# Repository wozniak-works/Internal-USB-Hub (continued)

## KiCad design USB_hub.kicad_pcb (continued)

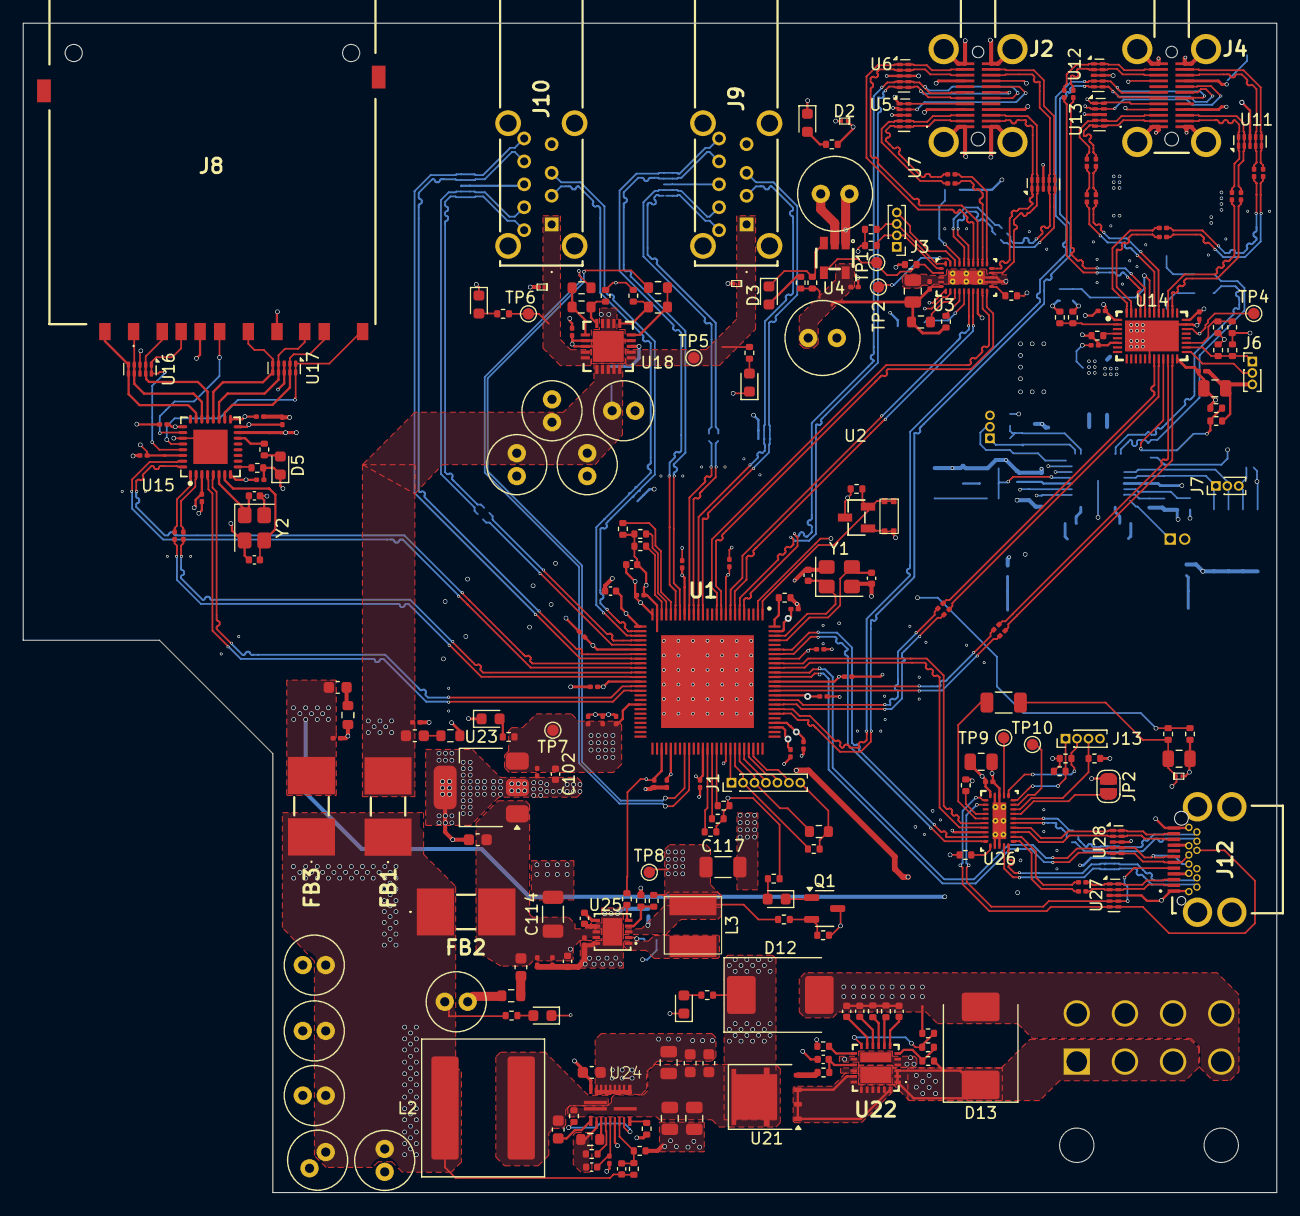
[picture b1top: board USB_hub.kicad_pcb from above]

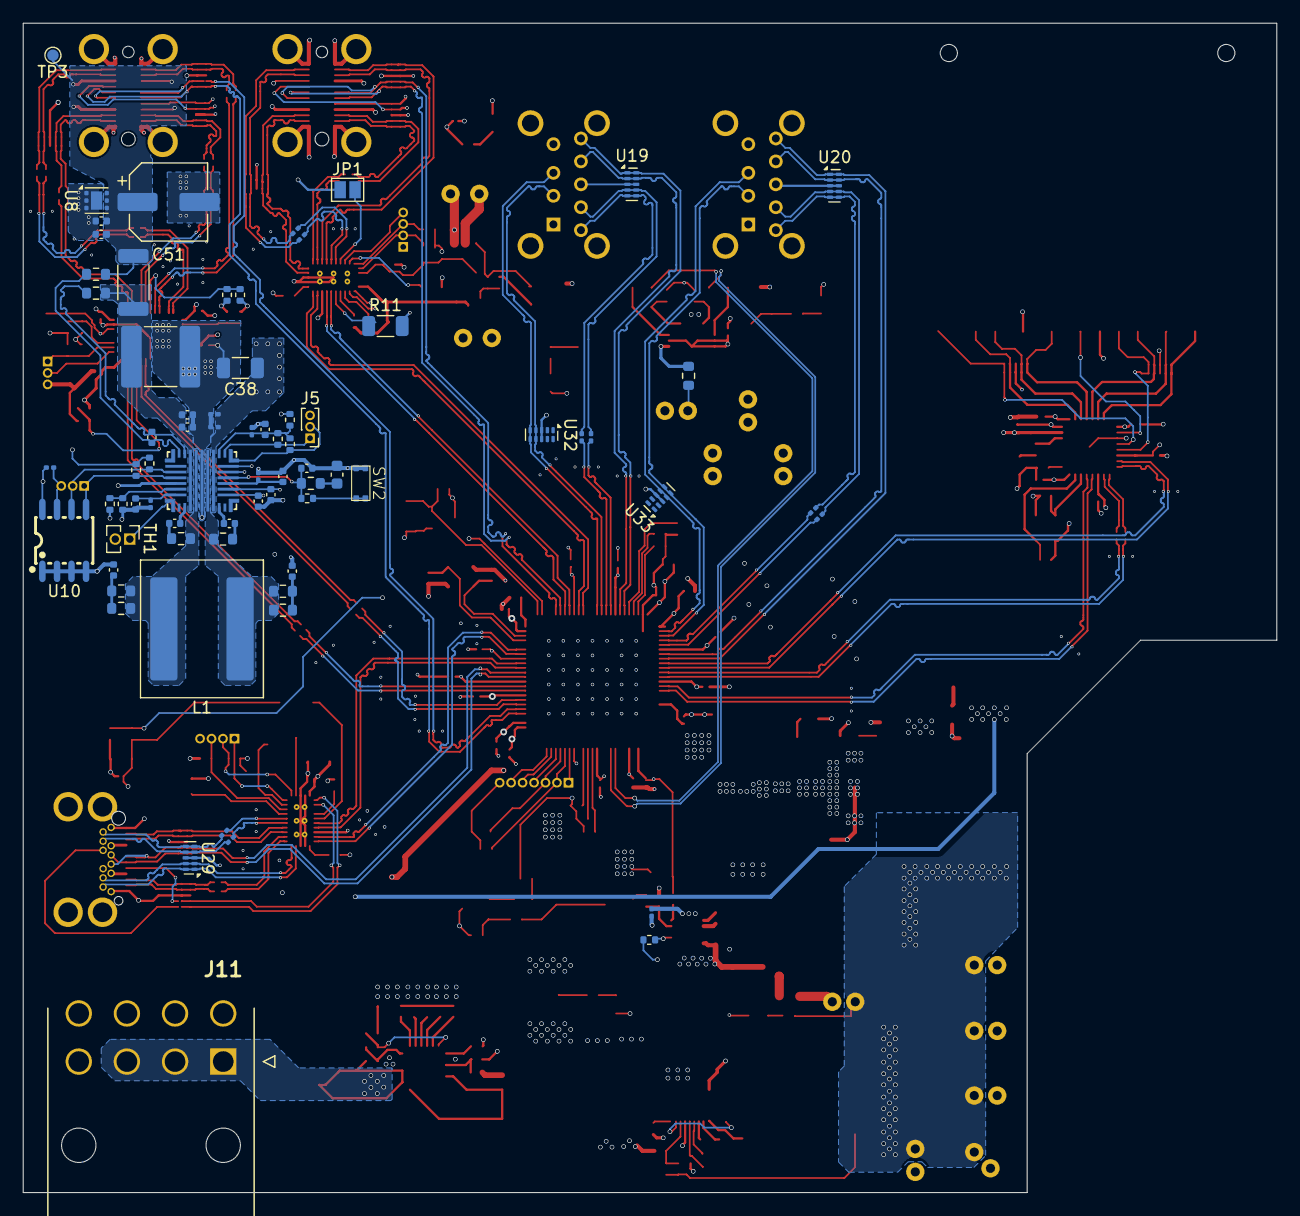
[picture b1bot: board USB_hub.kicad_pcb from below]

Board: 6 copper layers, 109.3 x 102.0 mm, 315 parts (72 on the bottom side), 244 nets.

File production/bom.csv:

Designator,Footprint,Quantity,Value,LCSC Part #
"C1, C103, C11, C112, C115, C116, C118, C12, C122, C123, C124, C125, C126, C127, C128, C129, C13, C130, C14, C15, C16, C17, C18, C2, C24, C25, C26, C27, C28, C3, C30, C33, C35, C37, C39, C4, C40, C5, C56, C6, C66, C67, C68, C69, C7, C70, C71, C72, C73, C76, C77, C8, C84, C86, C9, C92, C94",0201,57,0.1uF,C181043
"C10, C102, C19, C32, C34, C36",0402,6,4.7uF 10V,C318563
"C100, C101, C105, C85, C91, C93, C95, C99",0603,8,1uF,C5199872
C104,0402,1,820pF,C114386
"C106, C107, C108, C109, C110, C111, C80, C81, C82, C83",C_Radial_D5.0mm_H11.0mm_P2.00mm,10,47uF,C721300
C113,0402,1,22nF,C77023
"C114, C117, C38",1206,3,22uF 40V,C309062
C119,0402,1,2.2uF,C2999759
C120,0402,1,470pF,C272887
"C121, C23",0805,2,100uF (6.3V),C141660
"C20, C65, C96, C97, C98",0805,5,10uF,C3039694
"C21, C22, C78, C79",0402,4,18pF,C33149
C29,C_Radial_D6.3mm_H11.0mm_P2.50mm,1,150uF,C338186
C31,C_Radial_D6.3mm_H11.0mm_P2.50mm,1,120uF,C442816
"C41, C43, C46",0402,3,0.22uF (50V),C307445
"C42, C44, C45, C48, C49, C52, C53",0402,7,0.1uF (50V),C5182432
C47,0603,1,0.47uF 40V,C513577
C50,2220,1,33uF (50V),
C51,CP_Elec_6.3x7.7,1,100uF (50V),C311622
"C54, C55",0402,2,330pF,C325463
"C57, C58, C59, C60, C61, C62, C63, C64",0201,8,220nF,C701263
"C74, C75",0201,2,330nF,C2980695
"C87, C88",0402,2,2.2nF,C513667
C89,0402,1,8.20nF,C541457
C90,0402,1,4.7nF,C281757
"D1, D10, D2, D8",X2SON-2_L0.6-W0.3-P0.35,4,ESD441DPLR,C22427765
D12,D_SMC,1,B520C-13-F,C134460
D13,D_SMC,1,SMCJ12A,C224038
"D14, D15, D16, D17, D4, D5, D6, D7",0603,8,GREEN,C22371298
D3,0603,1,RED,C497918
"FB1, FB2, FB3",7427934,3,7427934,
"J10, J9",GSB4116344HR,2,USB3_A,C5429469
J11,45586-000Y,1,8-pin ATX connector,
J12,DX07S024XJ1R1100,1,USB_C_Receptacle,C134113
"J2, J4",USB420003A,2,USB_C_Receptacle,
J8,SD2A,1,SD_Card_Receptacle,
"L1, L2",L_Coilcraft_XAL1010-XXX,2,4.7uH,C18199458
L3,L_6.3x6.3_H3,1,1.5uH,C520330
Q1,SOT-23-3,1,MMBT2222A,C82460
R1,0402,1,12k 1%,C102781
"R10, R103, R12, R13, R9, R93, R94",0402,7,200k,C25764
"R100, R101",0402,2,10k,C2906974
"R102, R23, R24, R60, R61, R62, R63",0603,7,0,C2906974
R104,0603,1,10,C25764
"R11, R92",1206,2,900k,
"R14, R16, R2, R3, R4, R66, R7, R77, R83, R88, R89, R91",0402,12,10k,C25744
R15,0603,1,500k,C2902631
"R17, R78",0402,2,5k,C5948099
"R18, R20, R35, R36, R37, R38, R84, R95, R96, R97",0402,10,4.7k,C105871
"R19, R64, R65, R85",0402,4,1.5k,C327253
"R21, R22, R25, R26",0603,4,2.2 35V 0.25W,C966185
"R27, R29, R31",0603,3,10 (0.25W),C510088
R28,0402,1,6.65,C407669
R30,0402,1,120k,C93945
R32,2010,1,10m (1%),C844898
R33,0402,1,20k,C25765
"R34, R40, R43, R50",0402,4,1k,C11702
R39,0402,1,1k,C11702 
"R41, R42, R44, R47, R48, R49, R52, R53",0201,8,1,C166074
R45,0402,1,DNP,
"R46, R51, R54, R55, R56, R57",0402,6,R,
R5,0402,1,33k,C25779
"R58, R79",0402,2,680 1%,C25130
"R59, R82, R86",0402,3,560,C137858
R6,0402,1,50k,C166559
R67,0402,1,499k,C137971
"R68, R74, R75",0603,3,2,C2907139
R69,0402,1,200,C114764
R70,0402,1,27k,C138022
R71,0402,1,47k,C93943
R72,0402,1,100 1%,C106232
R73,0402,1,549 1%,C7334458
R76,0402,1,290k,C5126158
R8,0402,1,100k,C25741
R80,0402,1,243k,C2998149
R81,0603,1,8k,C862307
R87,0402,1,1M,C2906900
R90,0402,1,12k,C413006
SW1,ultra_small_switch_1.6x3.0mm,1,RESET_HUB,C913788
SW2,ultra_small_switch_1.6x3.0mm,1,FW_Upgrade,C913788
TH1,PinHeader_1x02_P1.27mm_Vertical,1,TMP61,
U1,QFN40P1200X1200X90-101N-D,1,USB7206C/KDX,
U10,SO-8_L4.9-W3.9-P1.27-LS5.9-BL,1,24LC256,C283433
"U11, U12, U13, U16, U17, U19, U20, U27, U28, U29, U32, U33, U5, U6, U7",USON-10_2.5x1.0mm_P0.5mm,15,TPD4E02B04DQA,C106794
U14,WQFN-40_L6.0-W4.0-P0.40-TL-EP,1,TUSB1142IRNQR_C5216209,C5216209
U15,HQFN-32_L5.0-W5.0-P0.50-BL-EP3.0,1,GL3224-OIY04,C157357
U18,QFN-20_L4.0-W4.0-P0.50-BL-EP2.7,1,UCS2113,C638222
U2,SOT-23-3_L2.9-W1.3-P1.90-LS2.4-BR,1,MIC803-29D4VM3-TR,C626154
U21,PowerPAK_SO-8L_Single,1,SiRA80DP,C3289458
U22,TPS259830ONRGER,1,TPS25983,C20611808
U23,SOT-223-3_TabPin2,1,AP7361C-33E-13,C500795
U24,MPS-QFN-21_3x4mm,1,MP8795,
U25,TDFN-10_L3.0-W3.0-P0.50-TL-EP,1,MIC23201YML-TR,C621769
"U26, U3",RNH0030A,2,HD3SS3220IRNHR,C165155
U4,TSOT-23-5_L2.9-W1.6-P0.95-LS2.8-BR,1,TPS2068EDBVR,C19272843
U8,WSON-6-1EP_2x2mm_P0.65mm_EP1x1.6mm,1,TVS2200DRV,C523793
U9,VQFN-HR-29_L6.0-W5.0-P0.50_TPS25762CQRQLRQ1,1,TPS25762CQRQLRQ1,C5986888
"Y1, Y2",Crystal_SMD_3225-4Pin_3.2x2.5mm,2,25MHz +-0.03%,C179643

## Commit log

2026-03-18 Design rule file added, lots of minor tweaks, routing done (including differential pairs), DRC done/
